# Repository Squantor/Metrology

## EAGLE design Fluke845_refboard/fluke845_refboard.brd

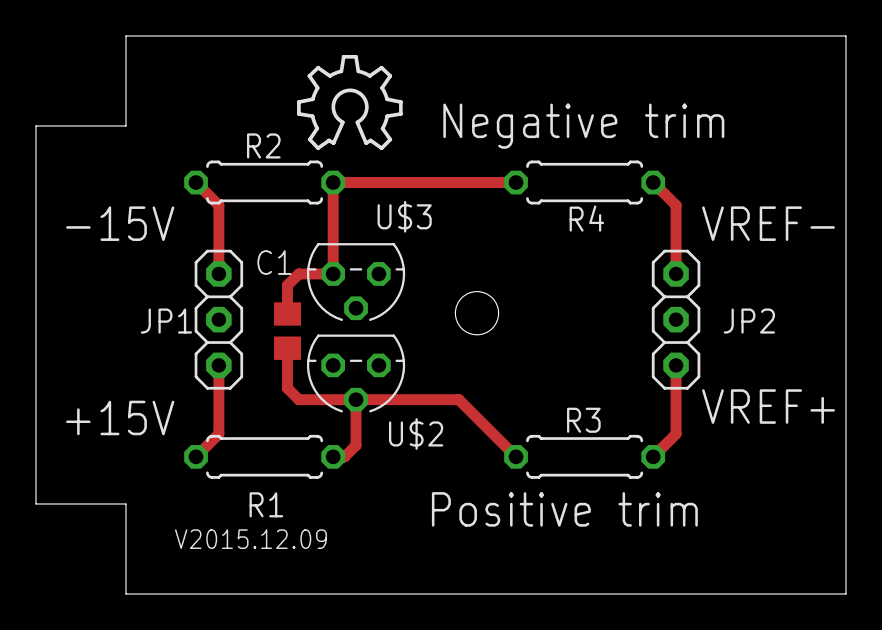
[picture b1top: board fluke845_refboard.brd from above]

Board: 2 copper layers, 45.0 x 31.0 mm, 11 parts (0 on the bottom side), 7 nets.

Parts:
C1: 10u; C0805
JP1, JP2: 1X03_SMALL
LOGO1: OSHW_LOGO_8MILX0200-NT; OSHW_8X200_NOTEXT
R1, R2: 33k; 0207/7
R3, R4: CALCULATE; 0207/7
U$1: SUPERTRONIC37_51; SUPERTRONIC_37_51MM
U$2, U$3: LT1004; TO92

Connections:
+15V: JP1.1, R1.2
-15V: JP1.3, R2.1
GND: JP1.2, JP2.2, U$2.1, U$3.2
unnamed: C1.2, R2.2, R4.2, U$3.1
unnamed: C1.1, R1.1, R3.1, U$2.2
VREF+: JP2.1, R3.2
VREF-: JP2.3, R4.1

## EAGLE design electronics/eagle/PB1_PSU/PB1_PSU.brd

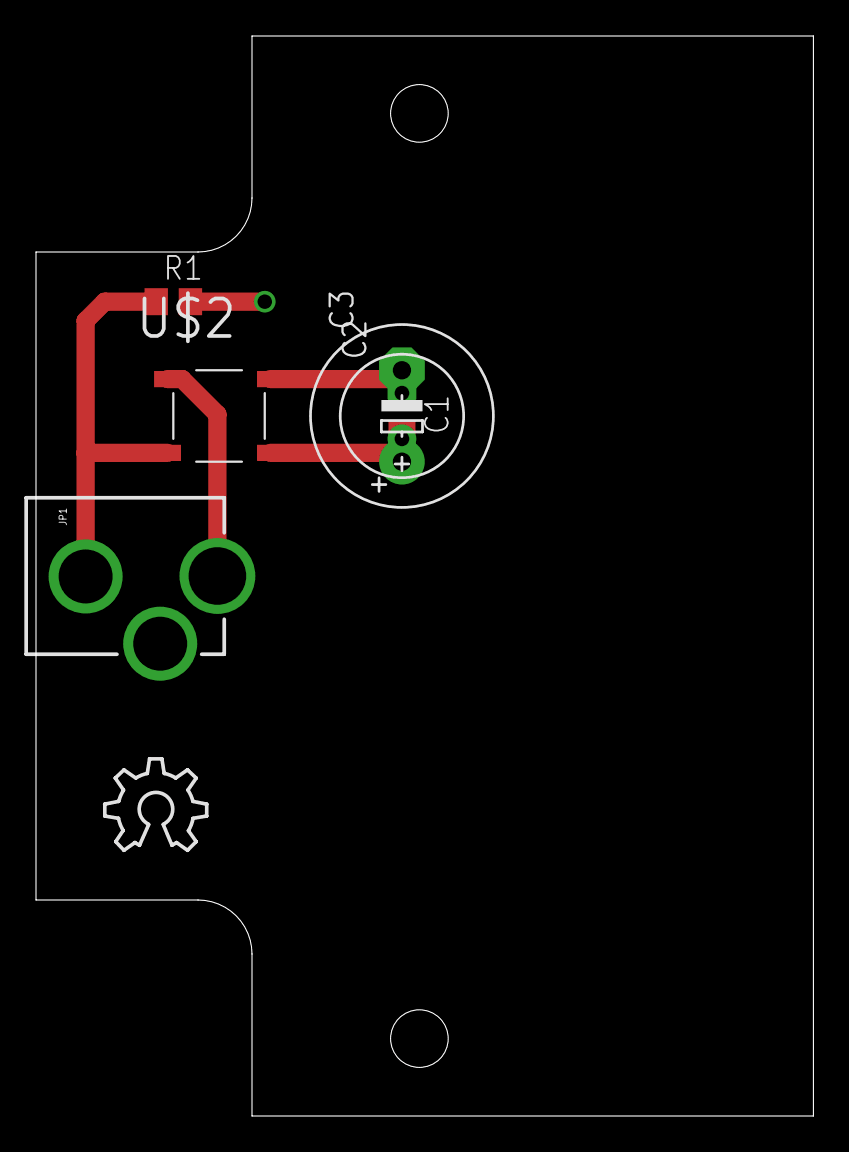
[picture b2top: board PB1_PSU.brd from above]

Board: 2 copper layers, 43.2 x 60.0 mm, 8 parts (0 on the bottom side), 4 nets.

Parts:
C1: C0805
C2: E2,5-7
C3: E5-10,5
JP1: POWER_JACKPTH_LOCK; POWER_JACK_PTH_LOCK
LOGO1: OSHW_LOGO_8MILX0200-NT; OSHW_8X200_NOTEXT
R1: R0805
U$1: FUTURLEC_PB1PB1_HALF; FUTURLEC_PB1_HALF
U$2: BRIDGE_RECTIFIERABS; ABS

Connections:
AC_EDGE: JP1.GND, R1.1, U$2.AC@2
AC_PIN: JP1.PWR, U$2.AC@1
GND: C1.1, C2.-, C3.-, R1.2, U$2.-
VRECT: C1.2, C2.+, C3.+, U$2.+

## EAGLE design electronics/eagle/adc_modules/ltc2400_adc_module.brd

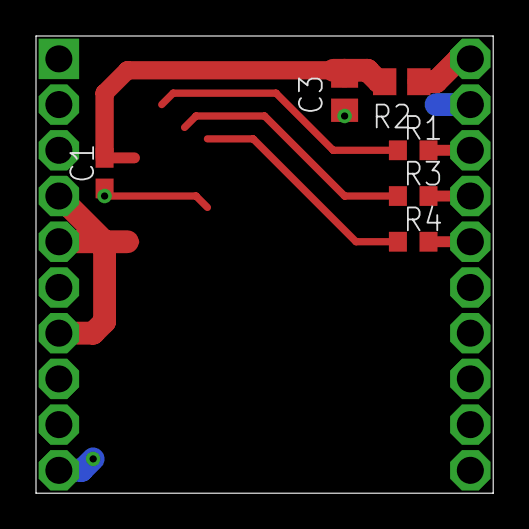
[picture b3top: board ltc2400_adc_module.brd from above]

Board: 2 copper layers, 25.4 x 25.4 mm, 7 parts (0 on the bottom side), 7 nets.

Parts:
C1: 100n; C0603
C3: 10u; C0805
R1, R3, R4: 100; R0603
R2: ferrite; R0805
U$1: METROLOGY_MODULE1.5MM; METROLOGY_MODULE_1.5MM_HOLE

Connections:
GND: C1.1, C3.1, U$1.P$6, U$1.P$10, U$1.P$19
unnamed: R2.1, U$1.P$20
unnamed: R1.2, U$1.P$18
unnamed: R3.2, U$1.P$17
unnamed: R4.2, U$1.P$16
VCC: C1.2, C3.2, R2.2
VREF: U$1.P$4, U$1.P$5, U$1.P$7
